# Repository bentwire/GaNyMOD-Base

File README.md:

# GaNyMOD-Base
Most basic GaNyMOD module.  Single GaN half bridge and driver: 0-30V, 0-20A(?), PE29102 Driver, EPC2102 GaN Half Bridge.

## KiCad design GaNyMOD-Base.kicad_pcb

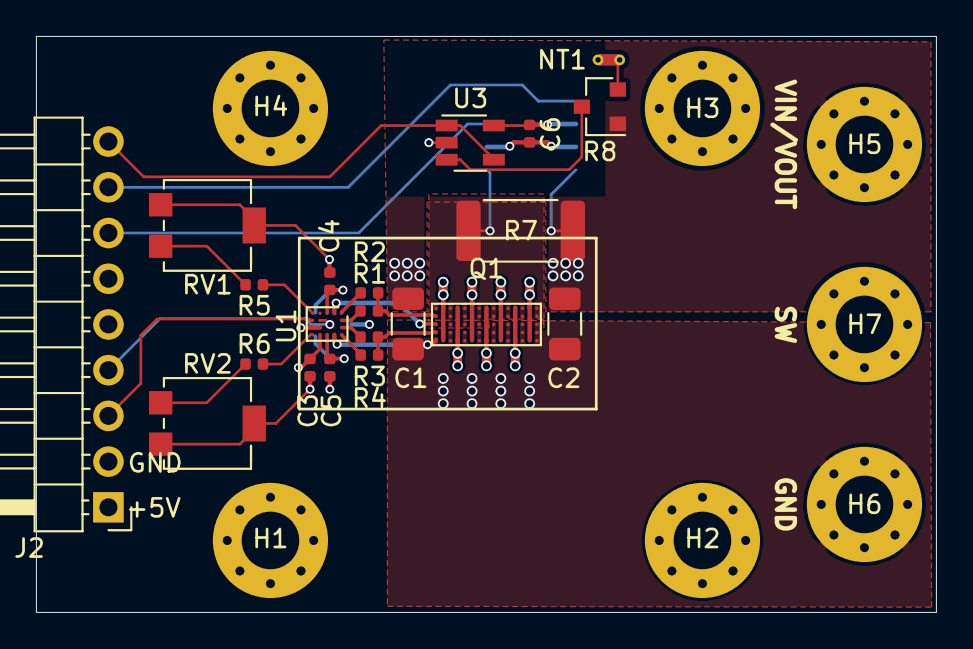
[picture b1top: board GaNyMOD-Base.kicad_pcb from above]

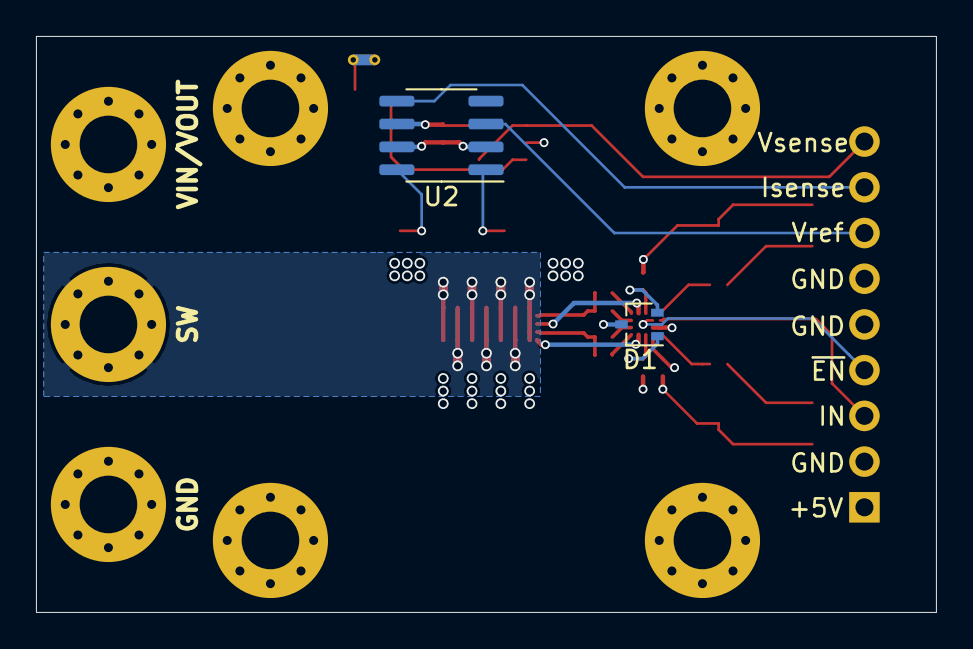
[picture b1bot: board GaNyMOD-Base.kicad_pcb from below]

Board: 4 copper layers, 50.0 x 32.0 mm, 30 parts (2 on the bottom side), 25 nets.

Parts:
C1, C2: 10uF 50V X5R; C_1206_3216Metric
C3, C4, C5, C6: 1uF 16V X5R; C_0402_1005Metric
D1: BAT54AW; SOT-323_SC-70
H1, H2, H3, H4, H5, H6, H7: MountingHole_Pad; MountingHole_3.2mm_M3_Pad_Via
J2: Conn_01x09_Male; PinHeader_1x09_P2.54mm_Horizontal
NT1: Net-Tie_2; NetTie-2_THT_Pad0.3mm
Q1: EPC2102; EPC2102-FC
R1, R2, R3, R4: 1R; R_0402_1005Metric
R5, R6: 30K; R_0402_1005Metric
R7: 0.010 Ohm; R_2512_6332Metric
R8: MPMT10019001AT1; SOT-23
RV1, RV2: 100K; Potentiometer_Bourns_3214G_Horizontal
U1: PE29102; pSemi_CSP-16_1.64x2.04mm_P0.4mm
U2: AD8216; SOIC-8_3.9x4.9mm_P1.27mm
U3: TLV3541; TSOT-23-5

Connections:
+5V: C3.1, C6.1, D1.3, J2.1, U1.15, U2.6, U3.5
+BATT: C1.1, C2.1, H5.1, R7.1, R8.1, U2.8
/IN: J2.3, U1.8
/Isense: J2.8, U2.5
/SW: H7.1, Q1.6, Q1.7, Q1.8, Q1.9, Q1.10, Q1.16, Q1.17, Q1.18, Q1.19, Q1.20, Q1.26, Q1.27, Q1.28, Q1.29, Q1.30, Q1.36, Q1.37, Q1.38, Q1.39, Q1.40, Q1.46, Q1.47, Q1.48, Q1.49, Q1.50, Q1.56, Q1.57, Q1.58, Q1.59, Q1.60, Q1.66, Q1.67, Q1.68, Q1.69, Q1.70
/Vref: J2.7, U2.3
/Vsense: J2.9, U3.1, U3.4
/Vss: Q1.1, Q1.11, Q1.12, Q1.13, Q1.21, Q1.22, Q1.23, Q1.31, Q1.32, Q1.33, Q1.41, Q1.42, Q1.51, Q1.52, Q1.61, Q1.62, Q1.71, Q1.72, R7.2, U2.1
/~EN~: J2.4, U1.7
GND: C3.2, C4.2, C5.2, C6.2, J2.2, J2.5, J2.6, NT1.1, RV1.2, RV1.3, RV2.1, RV2.2, U1.10, U1.11, U2.2, U2.7, U3.2
GNDPWR: C1.2, C2.2, H6.1, NT1.2, Q1.5, Q1.14, Q1.15, Q1.24, Q1.25, Q1.34, Q1.35, Q1.43, Q1.44, Q1.45, Q1.53, Q1.54, Q1.55, Q1.63, Q1.64, Q1.65, Q1.73, Q1.74, Q1.75, R8.2, U1.13
unnamed: C4.1, D1.2, U1.3
unnamed: C5.1, D1.1, U1.14
unnamed: Q1.2, R1.1, R2.1
unnamed: Q1.3, U1.2
unnamed: Q1.4, R3.1, R4.1
unnamed: R1.2, U1.6
unnamed: R2.2, U1.1
unnamed: R3.2, U1.9
unnamed: R4.2, U1.12
unnamed: R5.1, U1.5
unnamed: R5.2, RV1.1
unnamed: R6.1, U1.16
unnamed: R6.2, RV2.3
unnamed: R8.3, U3.3

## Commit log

2019-05-26 Initial import, PCB done, may need tweaks.
2019-05-29 Create LICENSE
